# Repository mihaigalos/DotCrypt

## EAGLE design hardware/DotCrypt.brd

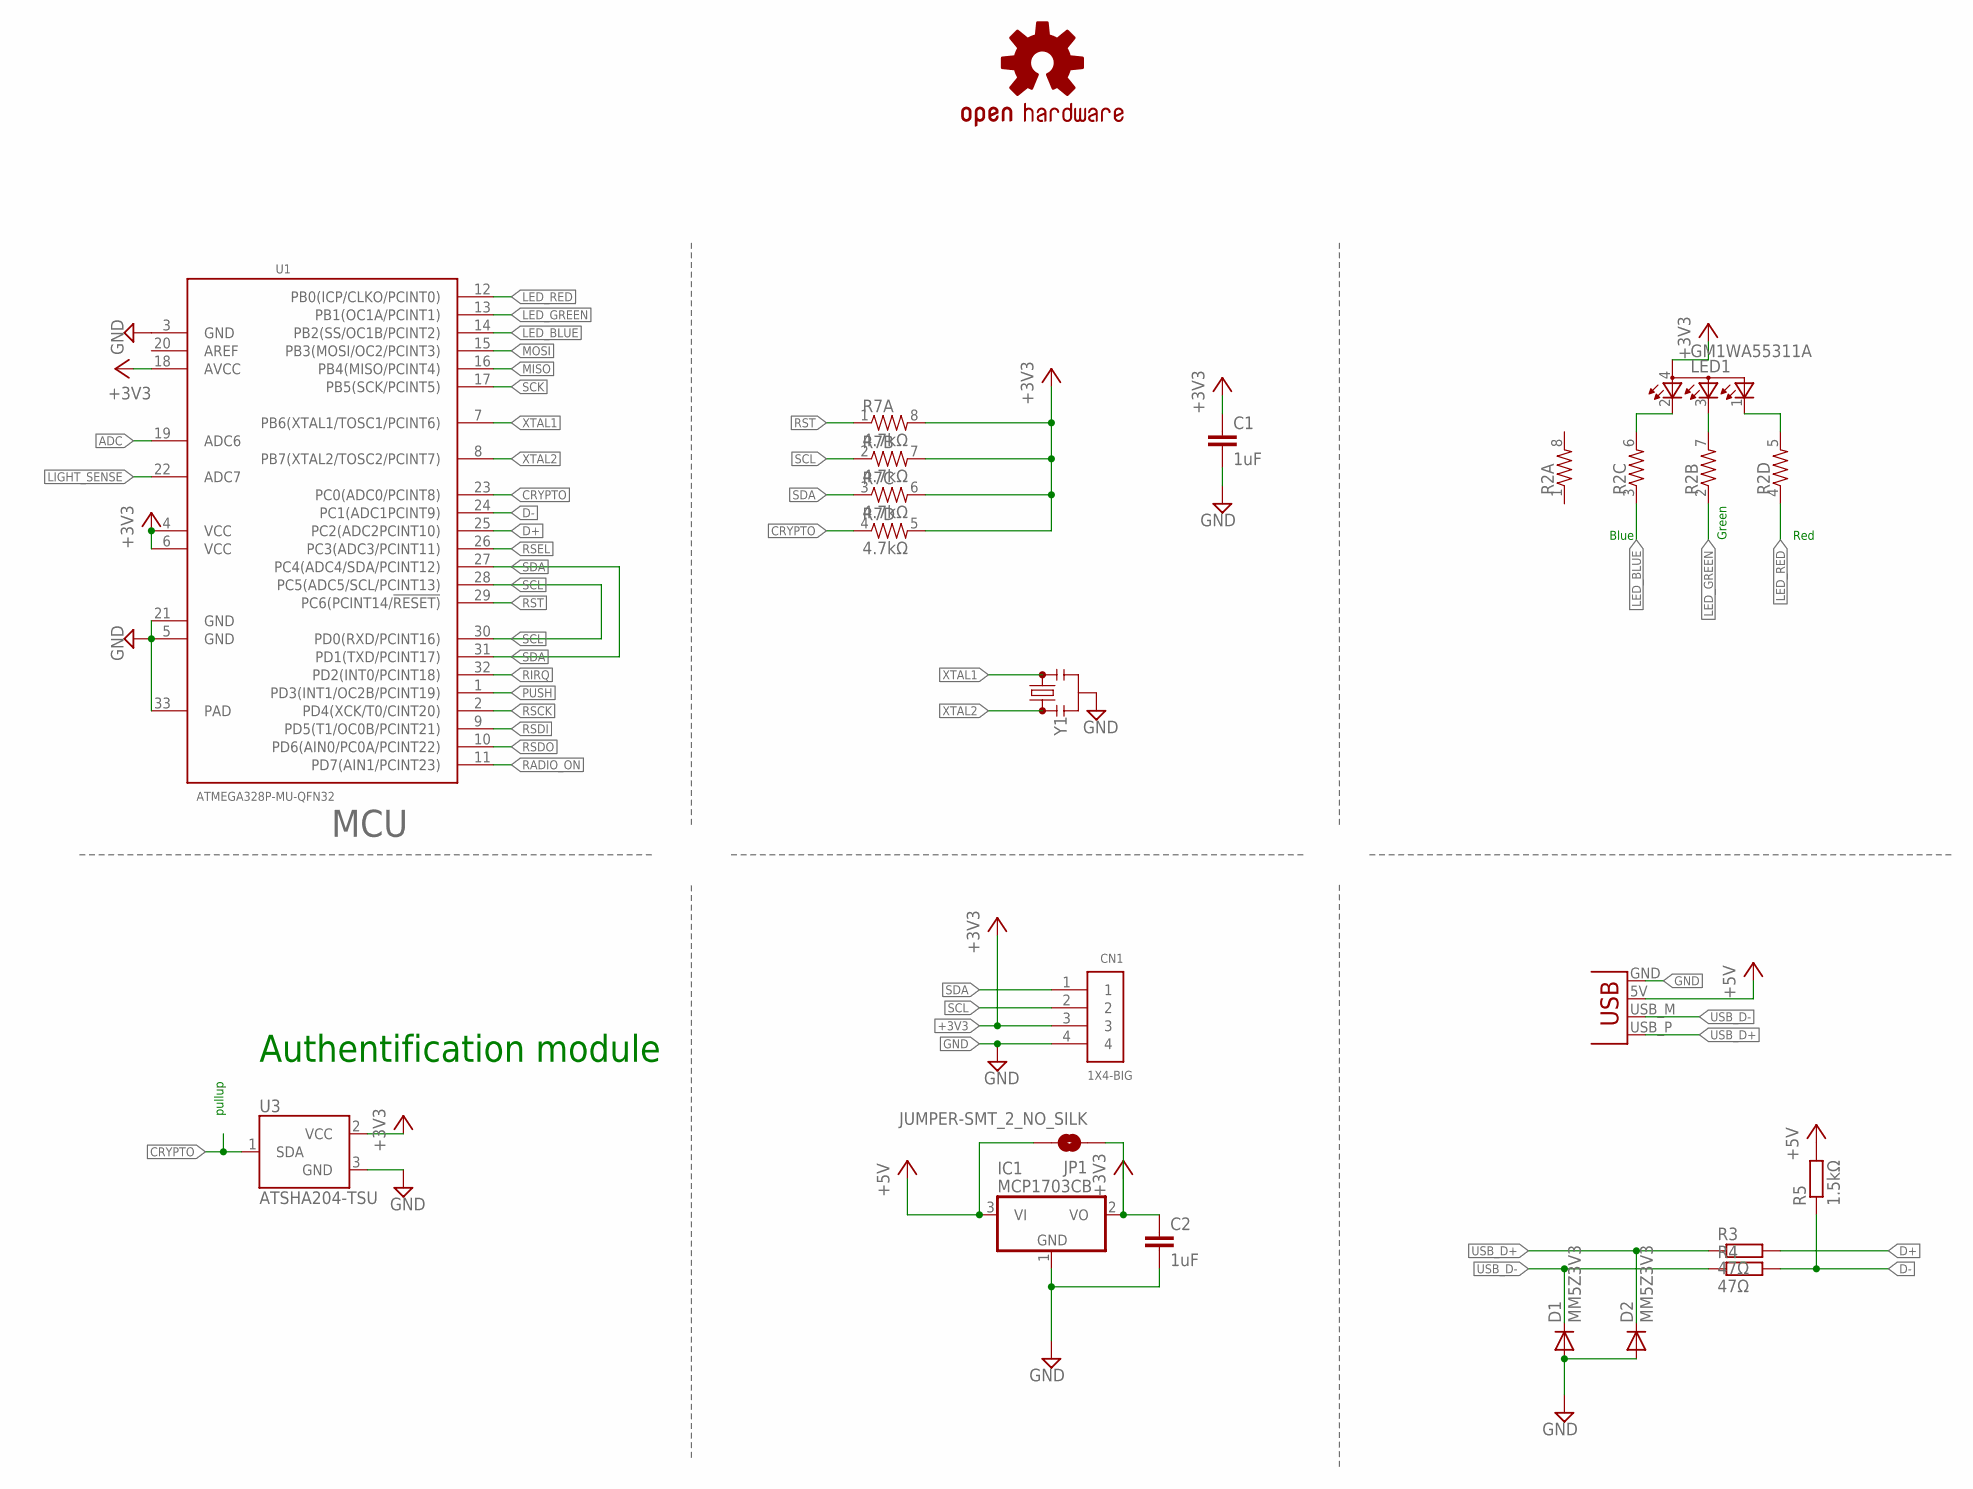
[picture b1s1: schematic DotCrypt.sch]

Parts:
C1, C2: 1uF; C0603
CN1: 1X4-BIG; 1X04-BIG
D1, D2: MM5Z3V3; SOD523
IC1: MCP1703CB; SOT23
JP1: JUMPER-SMT_2_NO_SILK; SMT-JUMPER_2_NO_SILK
JP3: USBPCB; USB-A-PCB
LED1: GM1WA55311A
LOGO1: OSHW-LOGOS; OSHW-LOGO-S
R2: RESISTOR-ARRAY0603-ARV; 0603-ARV
R3, R4: 47Ω; R0603
R5: 1.5kΩ; R0603
R7: 4.7kΩ; 0603-ARV
U1: ATMEGA328P-MU-QFN32; QFN32G-0.5-5X5MM
U3: ATSHA204-TSU; SOT23-3
Y1: RESONATORSMD-3.2X1.3; RESONATOR-SMD-3.2X1.3

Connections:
+3V3: C1.1, C2.1, CN1.3, IC1.2 (VO), JP1.1, LED1.4 (A), R7.5 (2), R7.6 (2), R7.7 (2), R7.8 (2), U1.4 (VCC), U1.6 (VCC), U1.18 (AVCC), U3.2 (VCC)
+5V: IC1.3 (VI), JP1.2, JP3.5V (VBUS), R5.2
ADC: U1.19 (ADC6)
BLUE: LED1.2 (CRED), R2.6 (2)
CRYPTO: R7.4 (1), U1.23 (PC0(ADC0/PCINT8)), U3.1 (SDA)
D+: R3.2, U1.25 (PC2(ADC2PCINT10))
D-: R4.2, R5.1, U1.24 (PC1(ADC1PCINT9))
GND: C1.2, C2.2, CN1.4, D1.A, D2.A, IC1.1 (GND), JP3.GND, U1.3 (GND), U1.5 (GND), U1.21 (GND), U1.33 (PAD), U3.3 (GND), Y1.2
GREEN: LED1.3 (CBLUE), R2.7 (2)
LED_BLUE: R2.3 (1), U1.14 (PB2(SS/OC1B/PCINT2))
LED_GREEN: R2.2 (1), U1.13 (PB1(OC1A/PCINT1))
LED_RED: R2.4 (1), U1.12 (PB0(ICP/CLKO/PCINT0))
LIGHT_SENSE: U1.22 (ADC7)
MISO: U1.16 (PB4(MISO/PCINT4))
MOSI: U1.15 (PB3(MOSI/OC2/PCINT3))
PUSH: U1.1 (PD3(INT1/OC2B/PCINT19))
RADIO_ON: U1.11 (PD7(AIN1/PCINT23))
RED: LED1.1 (CGREEN), R2.5 (2)
RIRQ: U1.32 (PD2(INT0/PCINT18))
RSCK: U1.2 (PD4(XCK/T0/CINT20))
RSDI: U1.9 (PD5(T1/OC0B/PCINT21))
RSDO: U1.10 (PD6(AIN0/PC0A/PCINT22))
RSEL: U1.26 (PC3(ADC3/PCINT11))
RST: R7.1, U1.29 (PC6(PCINT14/!RESET))
SCK: U1.17 (PB5(SCK/PCINT5))
SCL: CN1.2, R7.2 (1), U1.28 (PC5(ADC5/SCL/PCINT13)), U1.30 (PD0(RXD/PCINT16))
SDA: CN1.1, R7.3 (1), U1.27 (PC4(ADC4/SDA/PCINT12)), U1.31 (PD1(TXD/PCINT17))
USB_D+: D2.C, JP3.USB_P (D+), R3.1
USB_D-: D1.C, JP3.USB_M (D-), R4.1
XTAL1: U1.7 (PB6(XTAL1/TOSC1/PCINT6)), Y1.3
XTAL2: U1.8 (PB7(XTAL2/TOSC2/PCINT7)), Y1.1

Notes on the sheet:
MCU
Blue
Green
Red
Authentification module
pullup

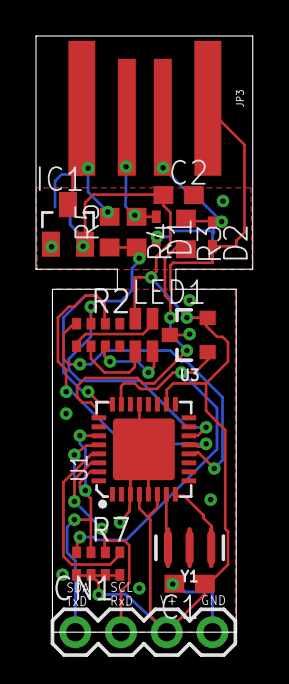
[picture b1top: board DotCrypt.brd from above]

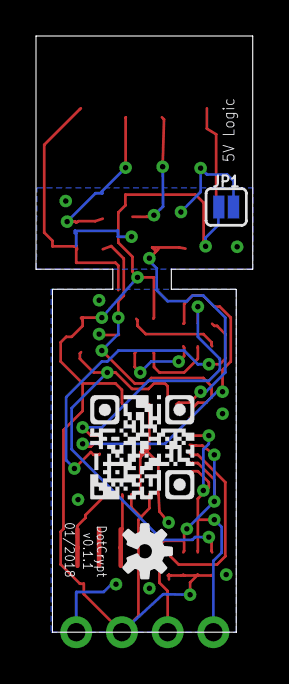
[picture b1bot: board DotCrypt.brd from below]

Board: 2 copper layers, 12.0 x 33.1 mm, 18 parts (2 on the bottom side), 19 nets.

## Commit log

2017-12-06 Overlapping I2C & UART pins
2017-12-06 Add GND planes
2017-12-06 Add decoupling cap, restructure connections
2017-12-06 Add QR, sch structure lines
2017-12-06 Amend: Add USB support
2017-12-06 Add OSHW logo, vTags, rearrange USB connections
2017-12-06 Adjust text logo
2017-12-06 Rearrange logos and pin connections
2017-12-06 Add USB D+ D- connections
2017-12-06 Add 3V3 regulator
2017-12-06 Reorder traces
2017-12-06 Add Measures

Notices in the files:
parts and their libraries:
SparkFun: Licensing: CC v3.0 Share-Alike You are welcome to use this library for commercial purposes.
SparkFun-IC-Special-Function: Licensing: Creative Commons ShareAlike 4.0 International - https://creativecommons.org/licenses/by-sa/4.0
